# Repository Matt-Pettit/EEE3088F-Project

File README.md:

# 🌡️ HAT for STM32F0: Temperature & Humidity Monitoring

# EEE3088F Group Project 10

Welcome to our **EEE3088F Group Project** repository! This repository contains all the project files for our HAT designed for the STM32F0 microcontroller. 

## 🚀 Project Overview

The primary functionality of the HAT is to monitor external environmental conditions using a digital Temperature and Humidity Sensor, along with an analogue light sensor (LDR)

This HAT has a wide range of potential applications. It would be particularly useful in monitoring for satisfactory growth conditions of plants in an agricultural setting. Secondly, the HAT may aid with maintaining optimum food and beverage storage conditions and therein reducing the amount of consumables that perish. Lastly, the HAT may be set to trigger air conditioning units and dehumidifiers in hospitals such that the patients may recuperate in a steady environment. 

## 🛠️ Hardware

The HAT is designed to attach to the STM32F051C6T6 microcontroller. The board includes circuitry to control power, the ability to be soft programmed and a standard pin interface on which the HAT will connect. 

## 🤝 Contributors

This project is being developed by three contributors:

- Queto Jenkins (Power Module)
- Holly Lewis (Sensor Module)
- Matt Pettit (Coding and Microcontroller Interfacing)

## 📁 Repository Contents

This repository contains the following files and folders:

- `README.md`: this file
- `Design-files`: folder containing the design files for the HAT
- `Source-code`: folder containing the source code for the HAT
- `LICENSE`: file containing license information
- `Bill Of Materials.xlsx`: BOM for this project

## 📝 License

This project is licensed under the GNU General Public License. See the LICENSE file for more information.

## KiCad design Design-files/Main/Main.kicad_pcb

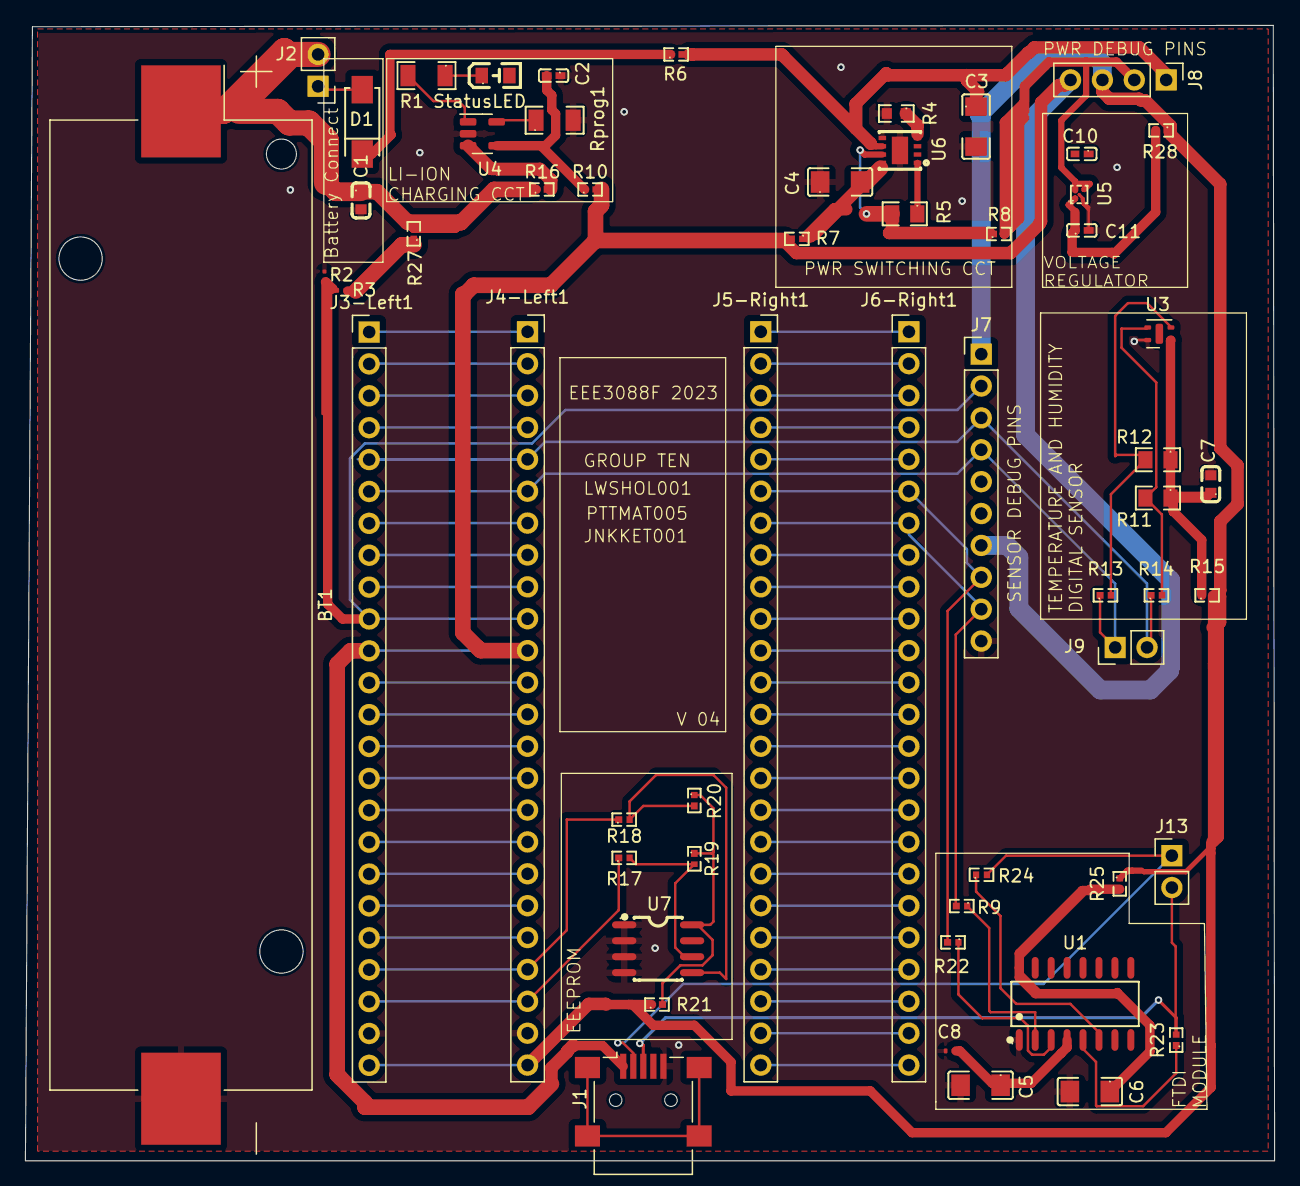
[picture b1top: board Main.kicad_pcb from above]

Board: 2 copper layers, 99.5 x 90.4 mm, 57 parts (0 on the bottom side), 78 nets.

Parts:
BT1: Battery_Cell; BatteryHolder_Keystone_1042_1x18650
C1, C7: 10 uF; C0603
C2, C10, C11: 1 uF; C0402
C3, C4: 0.1 uF; C1206
C5, C6: 0.1uF; C1206
C8: 0.1uF; C_0201_0603Metric
D1: D_Schottky; SMA_L4.2-W2.6-LS5.3-RD
J1: USB_B_Micro; USB_Mini-B_Lumberg_2486_01_Horizontal
J2: Battery Jumper; PinHeader_1x02_P2.54mm_Vertical
J3-Left1, J6-Right1: Conn_01x24_Pin; PinHeader_1x24_P2.54mm_Vertical
J4-Left1, J5-Right1: Conn_01x24_Socket; PinSocket_1x24_P2.54mm_Vertical
J7: Conn_01x10_Pin; PinHeader_1x10_P2.54mm_Vertical
J8: Conn_01x04_Pin; PinHeader_1x04_P2.54mm_Vertical
J9, J13: Conn_01x02_Pin; PinHeader_1x02_P2.54mm_Vertical
R1: 1k; R1206
R2, R3: 100K; R_0201_0603Metric
R4: 700; R0603
R5: 10K; R0805
R6, R7, R8, R9, R10, R13, R14, R15, R16, R17, R18, R21, R22, R23, R24, R25, R27, R28: 0; R0402
R11, R12: 10k; R0805
R19, R20: 4.7k; R0402
Rprog1: 1k; R1206
StatusLED: LED; LED0805-RD
U1: CH340C; SOP-16_L10.0-W3.9-P1.27-LS6.0-BL
U3: SHTC3; Sensirion_DFN-4-1EP_2x2mm_P1mm_EP0.7x1.6mm
U4: LTC4054ES5-4.2; TSOT-23-5
U5: RT9073A-33GQZ; ZQFN-4L_L1.0-W1.0-P0.63-BL-EP
U6: TPS2115ADRBR; SON-8_L3.0-W3.0-P0.65-LS3.0-BL-EP
U7: M24C64-RMN6TP; SOIC-8_L5.0-W4.0-P1.27-LS6.0-BL

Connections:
/BatterySense: J3-Left1.10, J4-Left1.10, J7.2, R2.1, R3.2
/DigitalSensorSCL: J3-Left1.6, J4-Left1.6, J7.4, J9.1, R13.1
/DigitalSensorSDA: J3-Left1.5, J4-Left1.5, J7.3, J9.2, R14.1
/Interfacing/EEPROMSCL: J3-Left1.21, J4-Left1.21, R18.1
/Interfacing/EEPROMSDA: J3-Left1.22, J4-Left1.22, R17.1
/Interfacing/USART_RX: J5-Right1.7, J6-Right1.7, J7.9, R9.2
/Interfacing/USART_TX: J5-Right1.6, J6-Right1.6, J7.8, R22.2
/Interfacing/USB D+: J1.3 (D+), J13.2, R23.2
/Interfacing/USB D-: J1.2 (D-), J13.1, R24.2
/Power Module/Battery Input Polarity Protection: C3.1, J8.1, R6.2, U6.6 (IN2)
/Power Module/Switched Power: J8.2, R8.2, U5.3 (EN), U5.4 (VIN)
/Regulated 3v3: J3-Left1.24, J4-Left1.24, J7.1, J8.3, R15.2, R21.1, R25.1, R28.1
/USB 5V: J1.1 (VBUS), J3-Left1.11, J4-Left1.11, J7.7, J8.4, R7.2, R10.2
Battery: BT1.1 (+), C1.1, J2.2, R16.1, R27.2
GND: BT1.2 (-), C1.2, C2.1, C3.2, C4.1, C5.2, C6.2, C7.2, C8.2, C11.2, J1.5 (GND), J3-Left1.23, J4-Left1.23, J7.10, R2.2, R4.2, Rprog1.2, U1.1 (GND), U3.4 (VSS), U4.2 (GND), U5.2 (GND), U5.5 (SGND), U6.5 (GND), U6.9 (GND), U7.1 (A0), U7.2 (A1), U7.3 (A2), U7.4 (VSS)
unnamed: C4.2, R7.1, U6.8 (IN1)
unnamed: R19.1, R20.1, R21.2, U7.8 (VCC)
unnamed: C2.2, R10.1, U4.4 (V_{CC})
unnamed: C7.1, R11.1, R12.1, R15.1, U3.1 (VDD)
unnamed: R1.1, StatusLED.1 (K)
unnamed: D1.2 (A), J2.1
unnamed: D1.1 (K), R6.1
unnamed: J3-Left1.1, J4-Left1.1
unnamed: J3-Left1.2, J4-Left1.2
unnamed: J3-Left1.3, J4-Left1.3
unnamed: J3-Left1.4, J4-Left1.4
unnamed: J3-Left1.7, J4-Left1.7
unnamed: J3-Left1.8, J4-Left1.8
unnamed: J3-Left1.9, J4-Left1.9
unnamed: J3-Left1.12, J4-Left1.12
unnamed: J3-Left1.13, J4-Left1.13
unnamed: J3-Left1.14, J4-Left1.14
unnamed: J3-Left1.15, J4-Left1.15
unnamed: J3-Left1.16, J4-Left1.16
unnamed: J3-Left1.17, J4-Left1.17
unnamed: J3-Left1.18, J4-Left1.18
unnamed: J3-Left1.19, J4-Left1.19
unnamed: J3-Left1.20, J4-Left1.20
unnamed: J5-Right1.1, J6-Right1.1
unnamed: J5-Right1.2, J6-Right1.2
unnamed: J5-Right1.3, J6-Right1.3
unnamed: J5-Right1.4, J6-Right1.4
unnamed: J5-Right1.5, J6-Right1.5
unnamed: J5-Right1.8, J6-Right1.8
unnamed: J5-Right1.9, J6-Right1.9
unnamed: J5-Right1.10, J6-Right1.10
unnamed: J5-Right1.11, J6-Right1.11
unnamed: J5-Right1.12, J6-Right1.12
unnamed: J5-Right1.13, J6-Right1.13
unnamed: J5-Right1.14, J6-Right1.14
unnamed: J5-Right1.15, J6-Right1.15
unnamed: J5-Right1.16, J6-Right1.16
unnamed: J5-Right1.17, J6-Right1.17
unnamed: J5-Right1.18, J6-Right1.18
unnamed: J5-Right1.19, J6-Right1.19
unnamed: J5-Right1.20, J6-Right1.20
unnamed: J5-Right1.21, J6-Right1.21
unnamed: J5-Right1.22, J6-Right1.22
unnamed: J5-Right1.23, J6-Right1.23
unnamed: J5-Right1.24, J6-Right1.24
unnamed: R3.1, R27.1
unnamed: R23.1, U1.5 (D+)
unnamed: R24.1, U1.6 (D-)
unnamed: R22.1, U1.3 (RXD)
unnamed: R9.1, U1.2 (TXD)
unnamed: C5.1, C8.1, U1.4 (V3)
unnamed: C6.1, R25.2, U1.16 (VCC)
unnamed: R12.2, R13.2, U3.2 (SCL)
unnamed: R11.2, R14.2, U3.3 (SDA)
unnamed: R16.2, U4.3 (BAT)
unnamed: Rprog1.1, U4.5 (PROG)
unnamed: R1.2, U4.1 (~CHRG)
unnamed: C11.1, R28.2, U5.1 (VOUT)
unnamed: R4.1, U6.4 (ILIM)
unnamed: R5.2, R8.1, U6.7 (OUT)
unnamed: R5.1, U6.1 (STAT)
unnamed: R17.2, R19.2, U7.6 (SCL)
unnamed: R18.2, R20.2, U7.5 (SDA)

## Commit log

2023-02-24 test
2023-02-24 Test commit
2023-02-24 Test commit 2
2023-02-24 Test commit 3
2023-02-24 my first commitment guys
2023-02-26 README.md Changes
2023-02-26 Some more basic changes to the README
2023-02-26 Added Folders
2023-02-26 Changes to our roles as contributors
2023-03-04 Schematic Changes
2023-03-04 Update Readme to reflect our choices
2023-03-11 Lots of changes :)
2023-03-11 Create CAD
2023-03-11 i am trying to maek a CAD folder
2023-03-11 added
2023-03-12 Generated New BOM
2023-03-13 The updated BOM
2023-03-18 lets go team
2023-03-19 hello
2023-03-20 lots of changes
2023-03-20 the labeling blocks added
2023-03-21 biggest change of my life
2023-04-13 fixed shematic
2023-04-13 gerbiees and silkscrenno
2023-04-13 zippy stuff for submission
2023-04-13 drill files again
2023-04-14 bom changes
2023-04-14 new zipped bom for the third final submission
2023-04-14 with lscs part numbees
2023-04-14 main
2023-04-14 last changes
2023-04-23 errata file added
